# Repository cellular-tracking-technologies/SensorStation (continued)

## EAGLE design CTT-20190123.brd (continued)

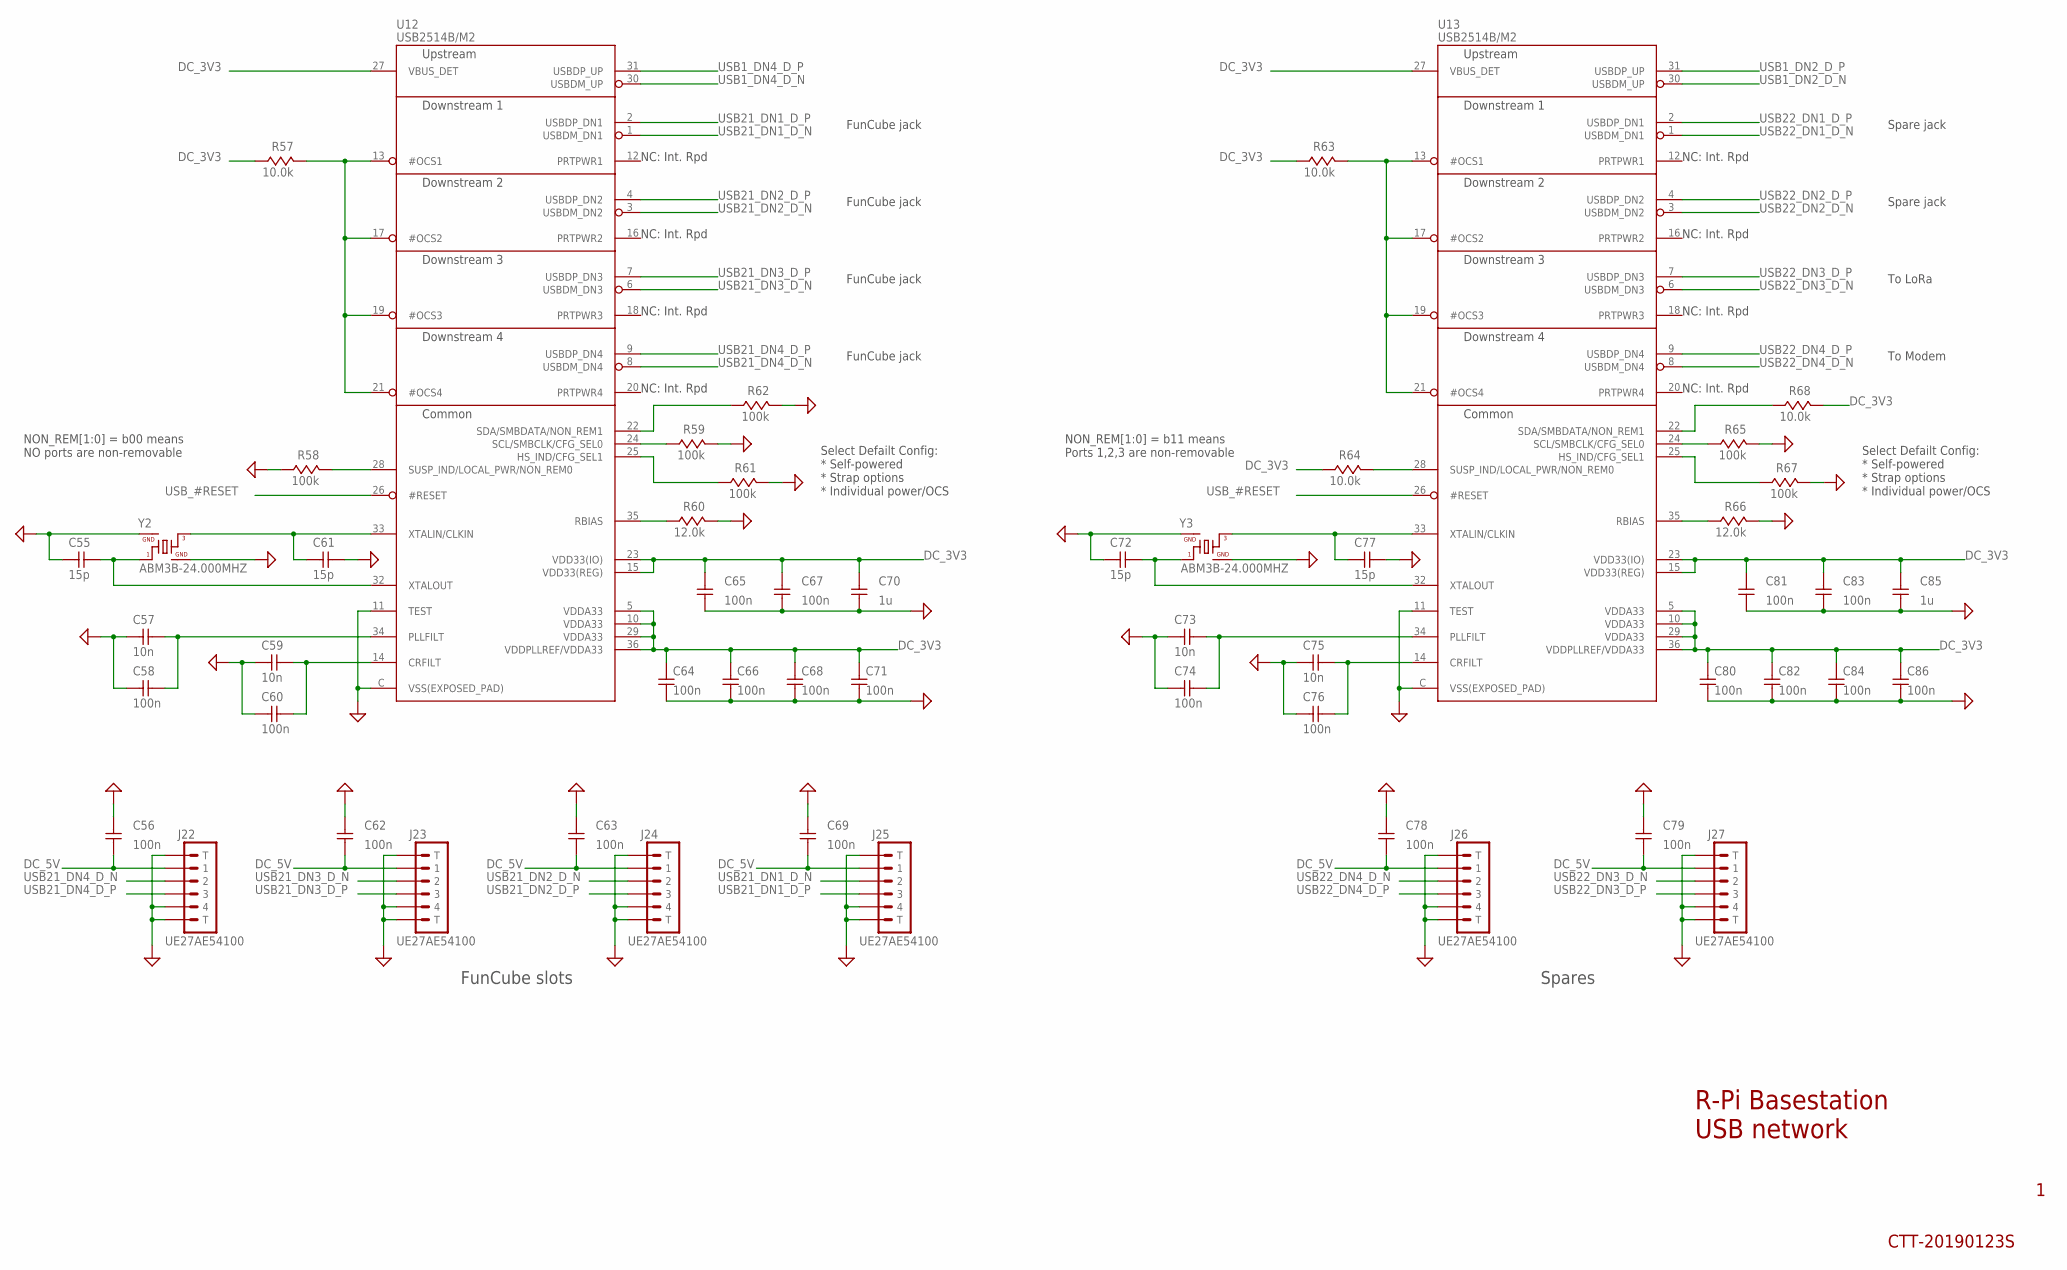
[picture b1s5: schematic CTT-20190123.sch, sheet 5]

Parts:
C55, C61, C72, C77: 15p; C0402_IPC7351_MED
C56, C58, C60, C62, C63, C64, C65, C66, C67, C68, C69, C71, C74, C76, C78, C79, C80, C81, C82, C83, C84, C86: 100n; C0402_IPC7351_MED
C57, C59, C73, C75: 10n; C0402_IPC7351_MED
C70, C85: 1u; C0603_IPC7351_MED
J22, J23, J24, J25, J26, J27: UE27AE54100
R57, R63, R64, R68: 10.0k; R0402_IPC7351_MED
R58, R59, R61, R62, R65, R67: 100k; R0402_IPC7351_MED
R60, R66: 12.0k; R0402_IPC7351_MED
U12, U13: USB2514B/M2; SQFN-36
Y2, Y3: ABM3B-24.000MHZ; ABM3B

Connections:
DC_3V3: C64.P$2 (2), C65.P$2 (2), C66.P$2 (2), C67.P$2 (2), C68.P$2 (2), C70.P$2 (2), C71.P$2 (2), C80.P$2 (2), C81.P$2 (2), C82.P$2 (2), C83.P$2 (2), C84.P$2 (2), C85.P$2 (2), C86.P$2 (2), R57.P$1 (1), R63.P$1 (1), R64.P$1 (1), R68.P$2 (2), U12.5 (VDDA33), U12.10 (VDDA33), U12.15 (VDD33(REG)), U12.23 (VDD33(IO)), U12.27 (VBUS_DET), U12.29 (VDDA33), U12.36 (VDDPLLREF/VDDA33), U13.5 (VDDA33), U13.10 (VDDA33), U13.15 (VDD33(REG)), U13.23 (VDD33(IO)), U13.27 (VBUS_DET), U13.29 (VDDA33), U13.36 (VDDPLLREF/VDDA33); also elsewhere on the board
DC_5V: C56.P$1 (1), C62.P$1 (1), C63.P$1 (1), C69.P$1 (1), C78.P$1 (1), C79.P$1 (1), J22.1, J23.1, J24.1, J25.1, J26.1, J27.1; also elsewhere on the board
GND: C55.P$1 (1), C56.P$2 (2), C57.P$1 (1), C58.P$1 (1), C59.P$1 (1), C60.P$1 (1), C61.P$2 (2), C62.P$2 (2), C63.P$2 (2), C64.P$1 (1), C65.P$1 (1), C66.P$1 (1), C67.P$1 (1), C68.P$1 (1), C69.P$2 (2), C70.P$1 (1), C71.P$1 (1), C72.P$1 (1), C73.P$1 (1), C74.P$1 (1), C75.P$1 (1), C76.P$1 (1), C77.P$2 (2), C78.P$2 (2), C79.P$2 (2), C80.P$1 (1), C81.P$1 (1), C82.P$1 (1), C83.P$1 (1), C84.P$1 (1), C85.P$1 (1), C86.P$1 (1), J22.4, J22.P$1 (T), J22.P$2 (T), J23.4, J23.P$1 (T), J23.P$2 (T), J24.4, J24.P$1 (T), J24.P$2 (T), J25.4, J25.P$1 (T), J25.P$2 (T), J26.4, J26.P$1 (T), J26.P$2 (T), J27.4, J27.P$1 (T), J27.P$2 (T), R58.P$1 (1), R59.P$2 (2), R60.P$2 (2), R61.P$2 (2), R62.P$2 (2), R65.P$2 (2), R66.P$2 (2), R67.P$2 (2), U12.11 (TEST), U12.C (VSS(EXPOSED_PAD)), U13.11 (TEST), U13.C (VSS(EXPOSED_PAD)), Y2.2, Y2.4, Y3.2, Y3.4; also elsewhere on the board
unnamed: C77.P$1 (1), U13.33 (XTALIN/CLKIN), Y3.3
unnamed: C72.P$2 (2), U13.32 (XTALOUT), Y3.1
unnamed: C61.P$1 (1), U12.33 (XTALIN/CLKIN), Y2.3
unnamed: C55.P$2 (2), U12.32 (XTALOUT), Y2.1
unnamed: C57.P$2 (2), C58.P$2 (2), U12.34 (PLLFILT)
unnamed: C73.P$2 (2), C74.P$2 (2), U13.34 (PLLFILT)
unnamed: C59.P$2 (2), C60.P$2 (2), U12.14 (CRFILT)
unnamed: R59.P$1 (1), U12.24 (SCL/SMBCLK/CFG_SEL0)
unnamed: C75.P$2 (2), C76.P$2 (2), U13.14 (CRFILT)
unnamed: R65.P$1 (1), U13.24 (SCL/SMBCLK/CFG_SEL0)
unnamed: R61.P$1 (1), U12.25 (HS_IND/CFG_SEL1)
unnamed: R67.P$1 (1), U13.25 (HS_IND/CFG_SEL1)
unnamed: R60.P$1 (1), U12.35 (RBIAS)
unnamed: R57.P$2 (2), U12.13 (#OCS1), U12.17 (#OCS2), U12.19 (#OCS3), U12.21 (#OCS4)
unnamed: R62.P$1 (1), U12.22 (SDA/SMBDATA/NON_REM1)
unnamed: R58.P$2 (2), U12.28 (SUSP_IND/LOCAL_PWR/NON_REM0)
unnamed: R66.P$1 (1), U13.35 (RBIAS)
unnamed: R63.P$2 (2), U13.13 (#OCS1), U13.17 (#OCS2), U13.19 (#OCS3), U13.21 (#OCS4)
unnamed: R68.P$1 (1), U13.22 (SDA/SMBDATA/NON_REM1)
unnamed: R64.P$2 (2), U13.28 (SUSP_IND/LOCAL_PWR/NON_REM0)
USB1_DN2_D_N: U13.30 (USBDM_UP); also elsewhere on the board
USB1_DN2_D_P: U13.31 (USBDP_UP); also elsewhere on the board
USB1_DN4_D_N: U12.30 (USBDM_UP); also elsewhere on the board
USB1_DN4_D_P: U12.31 (USBDP_UP); also elsewhere on the board
USB21_DN1_D_N: J25.2, U12.1 (USBDM_DN1)
USB21_DN1_D_P: J25.3, U12.2 (USBDP_DN1)
USB21_DN2_D_N: J24.2, U12.3 (USBDM_DN2)
USB21_DN2_D_P: J24.3, U12.4 (USBDP_DN2)
USB21_DN3_D_N: J23.2, U12.6 (USBDM_DN3)
USB21_DN3_D_P: J23.3, U12.7 (USBDP_DN3)
USB21_DN4_D_N: J22.2, U12.8 (USBDM_DN4)
USB21_DN4_D_P: J22.3, U12.9 (USBDP_DN4)
USB22_DN1_D_N: U13.1 (USBDM_DN1); also elsewhere on the board
USB22_DN1_D_P: U13.2 (USBDP_DN1); also elsewhere on the board
USB22_DN2_D_N: U13.3 (USBDM_DN2); also elsewhere on the board
USB22_DN2_D_P: U13.4 (USBDP_DN2); also elsewhere on the board
USB22_DN3_D_N: J27.2, U13.6 (USBDM_DN3)
USB22_DN3_D_P: J27.3, U13.7 (USBDP_DN3)
USB22_DN4_D_N: J26.2, U13.8 (USBDM_DN4)
USB22_DN4_D_P: J26.3, U13.9 (USBDP_DN4)
USB_#RESET: U12.26 (#RESET), U13.26 (#RESET); also elsewhere on the board

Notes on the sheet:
R-Pi Basestation USB network
CTT-20190123S
NC: Int. Rpd
Select Defailt Config: * Self-powered * Strap options * Individual power/OCS
NON_REM[1:0] = b00 means NO ports are non-removable
FunCube slots
NON_REM[1:0] = b11 means Ports 1,2,3 are non-removable
Spares
To Modem
To LoRa
Spare jack
FunCube jack

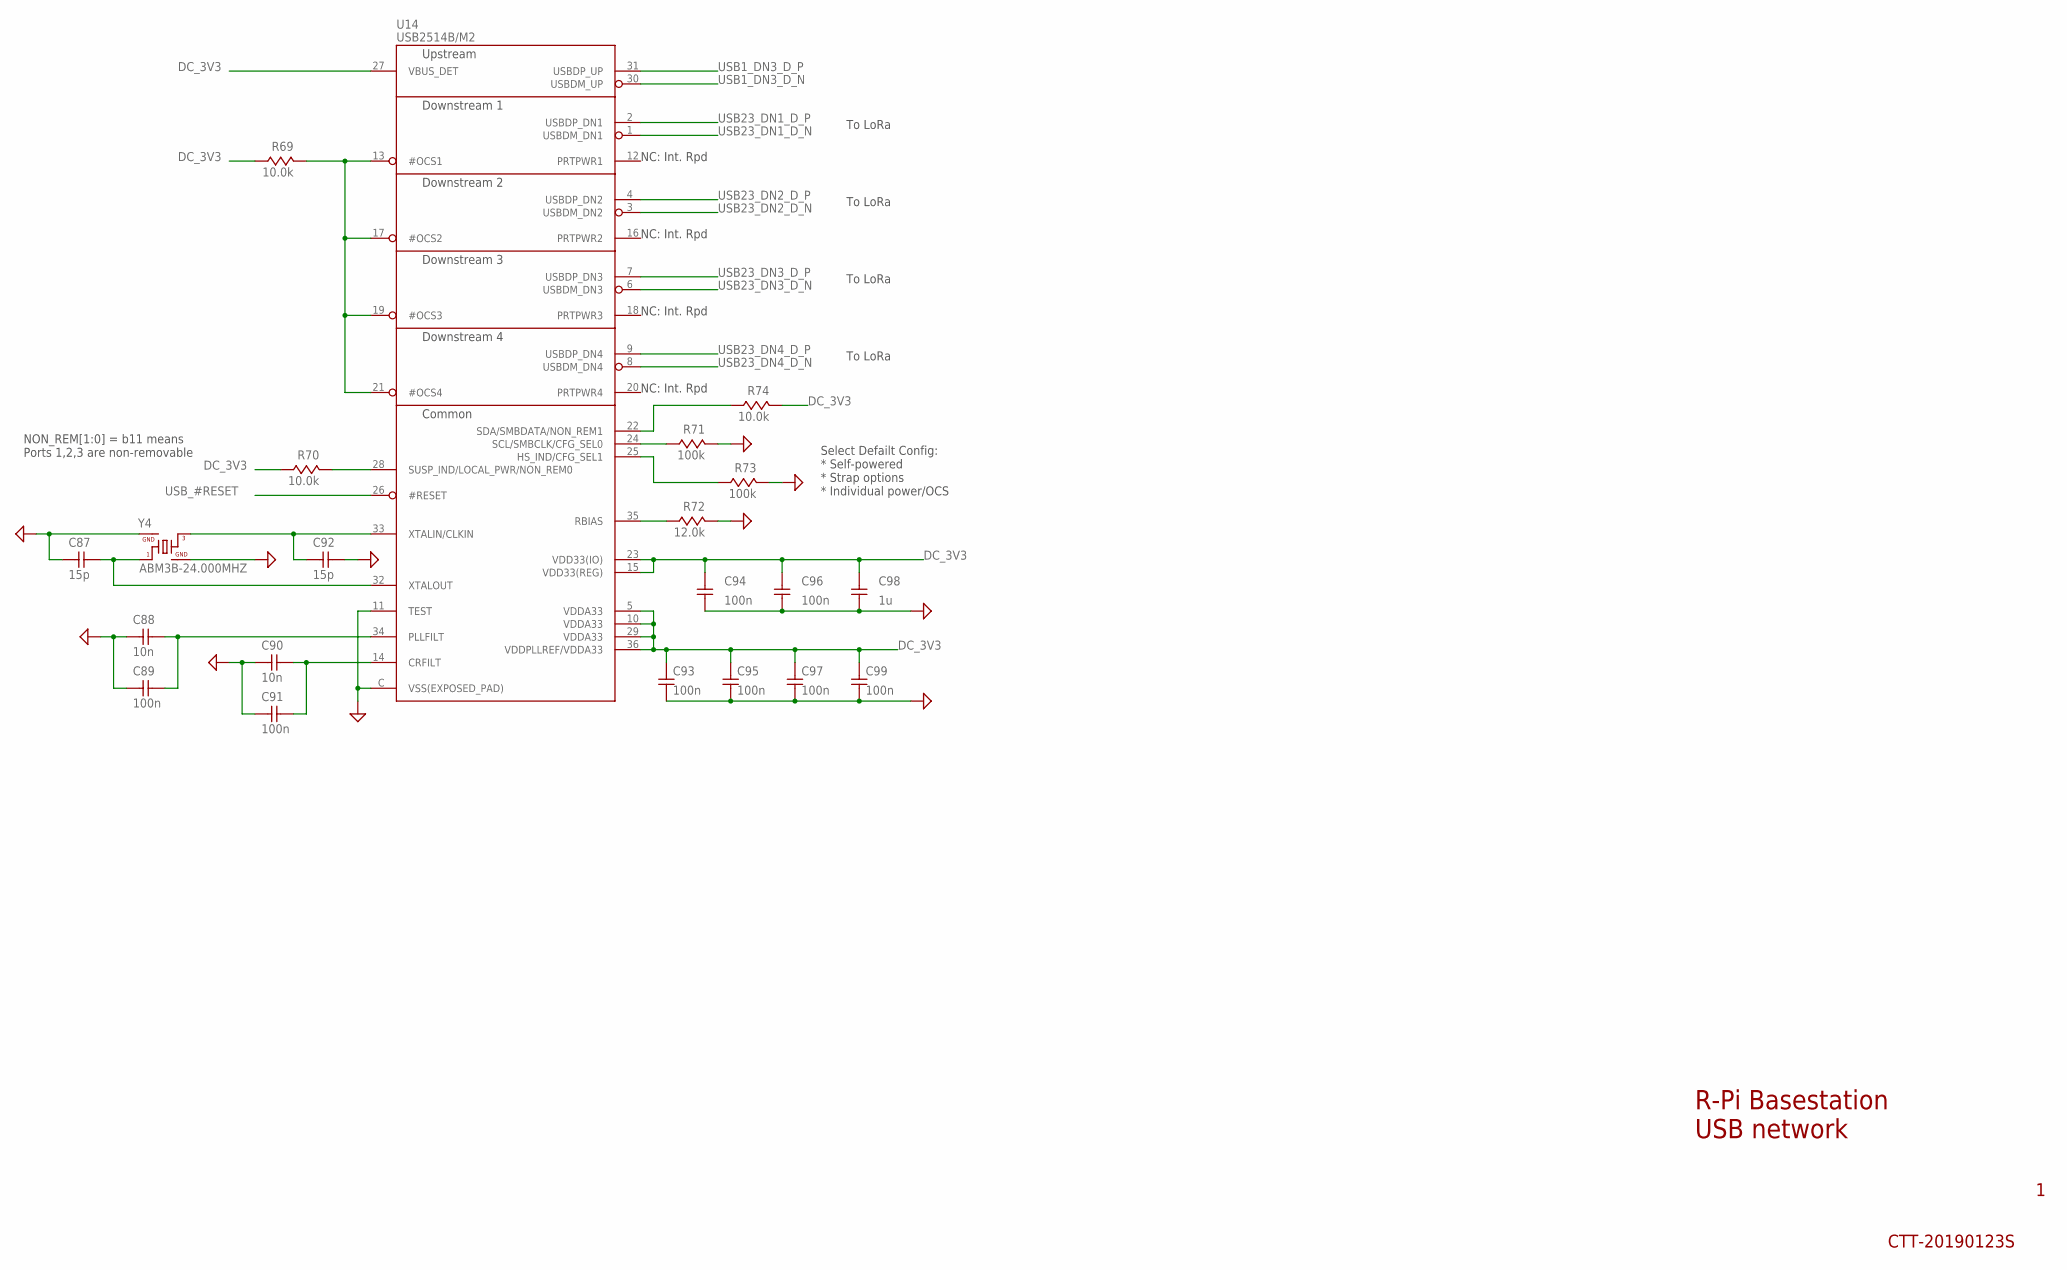
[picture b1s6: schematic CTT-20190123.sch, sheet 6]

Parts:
C87, C92: 15p; C0402_IPC7351_MED
C88, C90: 10n; C0402_IPC7351_MED
C89, C91, C93, C94, C95, C96, C97, C99: 100n; C0402_IPC7351_MED
C98: 1u; C0603_IPC7351_MED
R69, R70, R74: 10.0k; R0402_IPC7351_MED
R71, R73: 100k; R0402_IPC7351_MED
R72: 12.0k; R0402_IPC7351_MED
U14: USB2514B/M2; SQFN-36
Y4: ABM3B-24.000MHZ; ABM3B

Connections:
DC_3V3: C93.P$2 (2), C94.P$2 (2), C95.P$2 (2), C96.P$2 (2), C97.P$2 (2), C98.P$2 (2), C99.P$2 (2), R69.P$1 (1), R70.P$1 (1), R74.P$2 (2), U14.5 (VDDA33), U14.10 (VDDA33), U14.15 (VDD33(REG)), U14.23 (VDD33(IO)), U14.27 (VBUS_DET), U14.29 (VDDA33), U14.36 (VDDPLLREF/VDDA33); also elsewhere on the board
GND: C87.P$1 (1), C88.P$1 (1), C89.P$1 (1), C90.P$1 (1), C91.P$1 (1), C92.P$2 (2), C93.P$1 (1), C94.P$1 (1), C95.P$1 (1), C96.P$1 (1), C97.P$1 (1), C98.P$1 (1), C99.P$1 (1), R71.P$2 (2), R72.P$2 (2), R73.P$2 (2), U14.11 (TEST), U14.C (VSS(EXPOSED_PAD)), Y4.2, Y4.4; also elsewhere on the board
unnamed: C92.P$1 (1), U14.33 (XTALIN/CLKIN), Y4.3
unnamed: C87.P$2 (2), U14.32 (XTALOUT), Y4.1
unnamed: C88.P$2 (2), C89.P$2 (2), U14.34 (PLLFILT)
unnamed: C90.P$2 (2), C91.P$2 (2), U14.14 (CRFILT)
unnamed: R71.P$1 (1), U14.24 (SCL/SMBCLK/CFG_SEL0)
unnamed: R73.P$1 (1), U14.25 (HS_IND/CFG_SEL1)
unnamed: R72.P$1 (1), U14.35 (RBIAS)
unnamed: R69.P$2 (2), U14.13 (#OCS1), U14.17 (#OCS2), U14.19 (#OCS3), U14.21 (#OCS4)
unnamed: R74.P$1 (1), U14.22 (SDA/SMBDATA/NON_REM1)
unnamed: R70.P$2 (2), U14.28 (SUSP_IND/LOCAL_PWR/NON_REM0)
USB1_DN3_D_N: U14.30 (USBDM_UP); also elsewhere on the board
USB1_DN3_D_P: U14.31 (USBDP_UP); also elsewhere on the board
USB23_DN1_D_N: U14.1 (USBDM_DN1); also elsewhere on the board
USB23_DN1_D_P: U14.2 (USBDP_DN1); also elsewhere on the board
USB23_DN2_D_N: U14.3 (USBDM_DN2); also elsewhere on the board
USB23_DN2_D_P: U14.4 (USBDP_DN2); also elsewhere on the board
USB23_DN3_D_N: U14.6 (USBDM_DN3); also elsewhere on the board
USB23_DN3_D_P: U14.7 (USBDP_DN3); also elsewhere on the board
USB23_DN4_D_N: U14.8 (USBDM_DN4); also elsewhere on the board
USB23_DN4_D_P: U14.9 (USBDP_DN4); also elsewhere on the board
USB_#RESET: U14.26 (#RESET); also elsewhere on the board

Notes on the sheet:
R-Pi Basestation USB network
CTT-20190123S
NC: Int. Rpd
Select Defailt Config: * Self-powered * Strap options * Individual power/OCS
NON_REM[1:0] = b11 means Ports 1,2,3 are non-removable
To LoRa

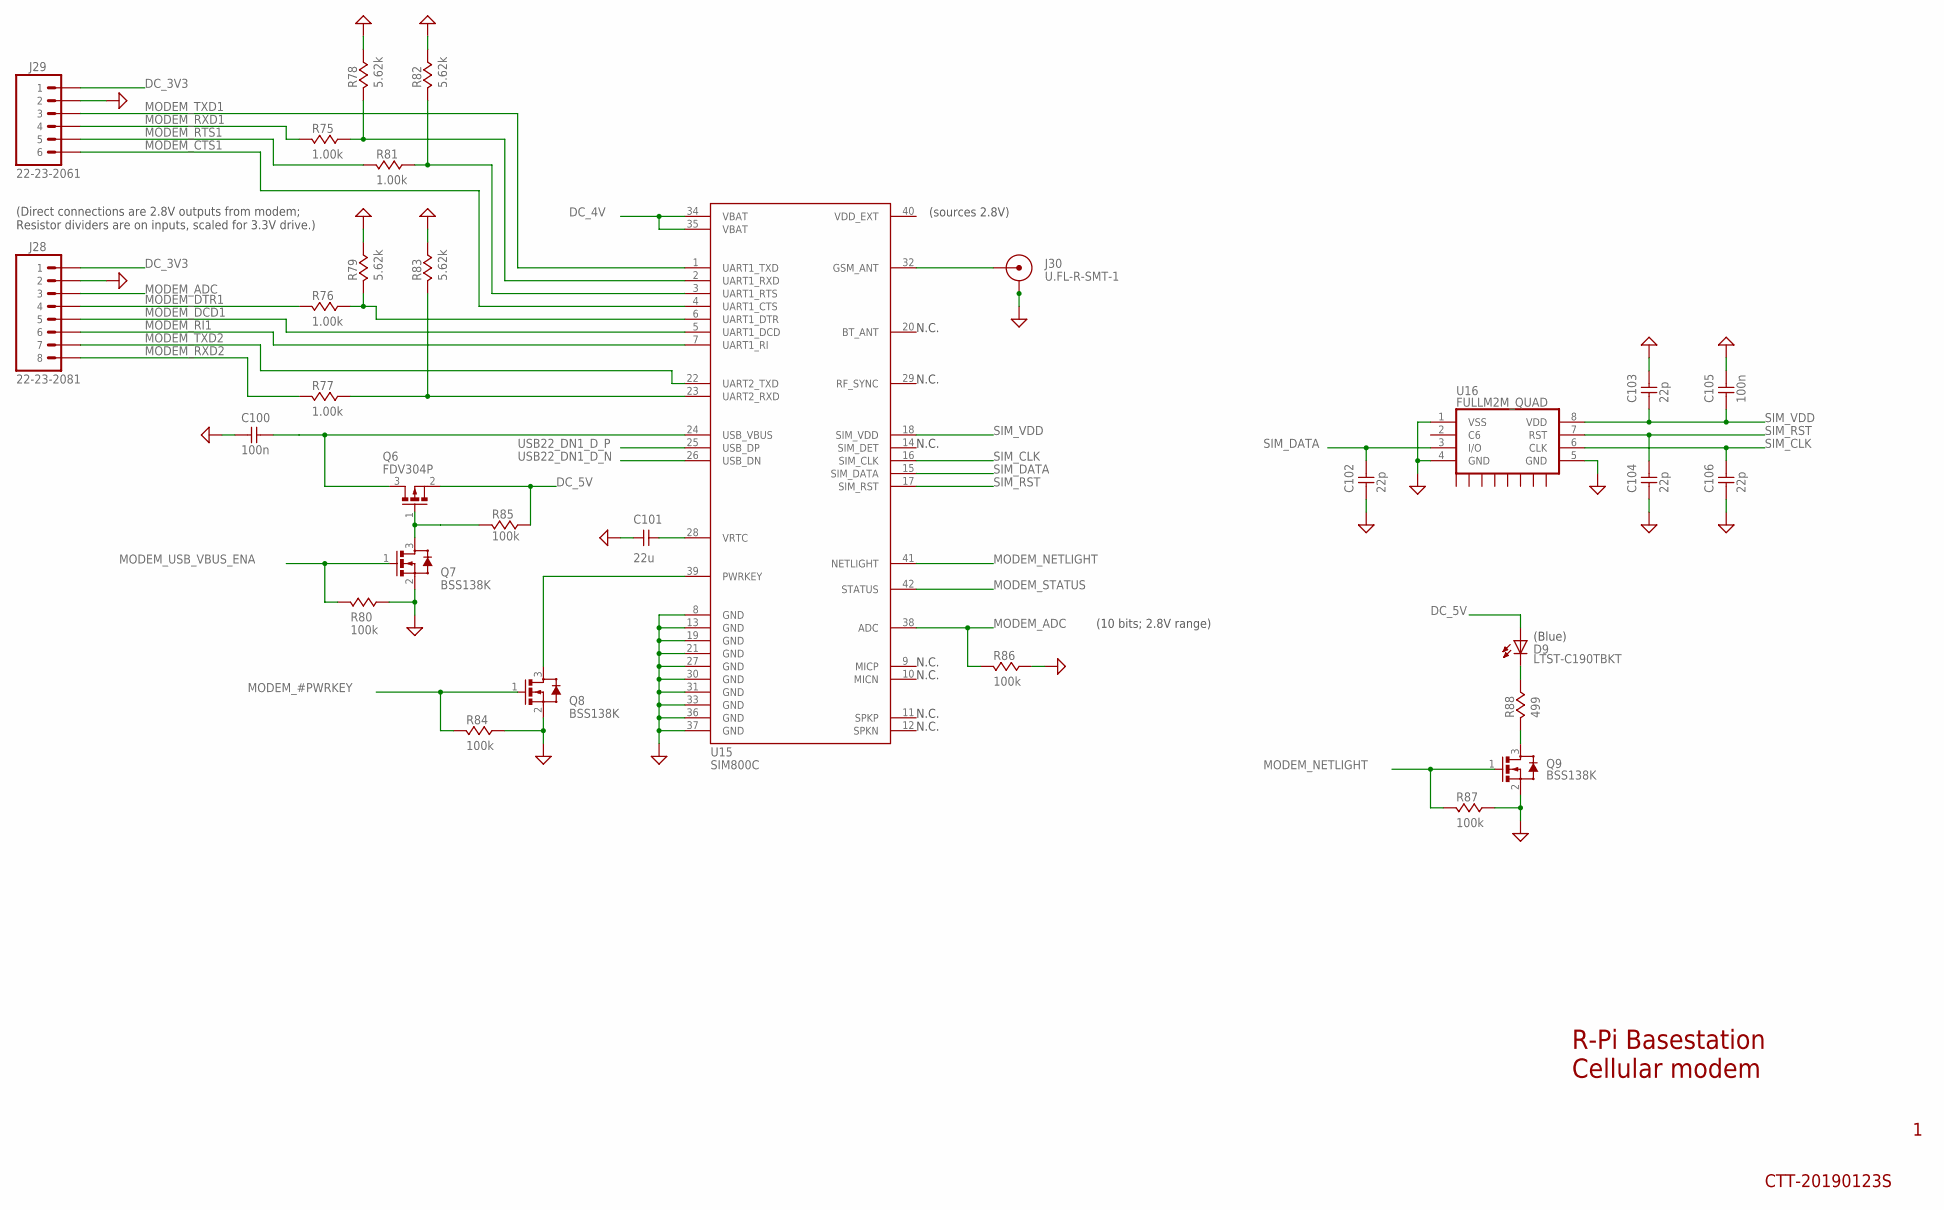
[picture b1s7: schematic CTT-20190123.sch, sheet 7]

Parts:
C100, C105: 100n; C0402_IPC7351_MED
C101: 22u; C0805
C102, C103, C104, C106: 22p; C0402_IPC7351_MED
D9: LTST-C190TBKT; LED0603
J28: 22-23-2081; MTA100-8
J29: 22-23-2061; MTA100-6
J30: U.FL-R-SMT-1
Q6: FDV304P; SOT-23
Q7, Q8, Q9: BSS138K; SOT-23
R75, R76, R77, R81: 1.00k; R0402_IPC7351_MED
R78, R79, R82, R83: 5.62k; R0402_IPC7351_MED
R80, R84, R85, R86, R87: 100k; R0402_IPC7351_MED
R88: 499; R0402_IPC7351_MED
U15: SIM800C
U16: FULLM2M_QUAD; MFF2

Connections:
DC_3V3: J28.1, J29.1; also elsewhere on the board
DC_4V: U15.34 (VBAT), U15.35 (VBAT); also elsewhere on the board
DC_5V: D9.A, Q6.2 (S), R85.P$1 (1); also elsewhere on the board
GND: C100.P$1 (1), C101.1, C102.P$1 (1), C103.P$2 (2), C104.P$1 (1), C105.P$2 (2), C106.P$1 (1), J28.2, J29.2, J30.GND, J30.GND@1 (GND), Q7.2 (S), Q8.2 (S), Q9.2 (S), R78.P$1 (1), R79.P$1 (1), R80.P$1 (1), R82.P$1 (1), R83.P$1 (1), R84.P$1 (1), R86.P$1 (1), R87.P$1 (1), U15.8 (GND), U15.13 (GND), U15.19 (GND), U15.21 (GND), U15.27 (GND), U15.30 (GND), U15.31 (GND), U15.33 (GND), U15.36 (GND), U15.37 (GND), U16.1 (VSS), U16.4 (GND), U16.5 (GND); also elsewhere on the board
MODEM_#PWRKEY: Q8.1 (G), R84.P$2 (2); also elsewhere on the board
MODEM_ADC: J28.3, R86.P$2 (2), U15.38 (ADC)
MODEM_CTS1: J29.6, U15.4 (UART1_CTS); also elsewhere on the board
MODEM_DCD1: J28.5, U15.5 (UART1_DCD)
MODEM_DTR1: J28.4, R76.P$2 (2)
MODEM_NETLIGHT: Q9.1 (G), R87.P$2 (2), U15.41 (NETLIGHT)
MODEM_RI1: J28.6, U15.7 (UART1_RI)
MODEM_RTS1: J29.5, R81.P$2 (2); also elsewhere on the board
MODEM_RXD1: J29.4, R75.P$2 (2); also elsewhere on the board
MODEM_RXD2: J28.8, R77.P$2 (2)
MODEM_STATUS: U15.42 (STATUS); also elsewhere on the board
MODEM_TXD1: J29.3, U15.1 (UART1_TXD); also elsewhere on the board
MODEM_TXD2: J28.7, U15.22 (UART2_TXD)
MODEM_USB_VBUS_ENA: Q7.1 (G), R80.P$2 (2); also elsewhere on the board
unnamed: Q8.3 (D), U15.39 (PWRKEY)
unnamed: C101.2, U15.28 (VRTC)
unnamed: C100.P$2 (2), Q6.3 (D), U15.24 (USB_VBUS)
unnamed: R77.P$1 (1), R83.P$2 (2), U15.23 (UART2_RXD)
unnamed: Q6.1 (G), Q7.3 (D), R85.P$2 (2)
unnamed: J30.SIG, U15.32 (GSM_ANT)
unnamed: R76.P$1 (1), R79.P$2 (2), U15.6 (UART1_DTR)
unnamed: D9.K, R88.P$1 (1)
unnamed: Q9.3 (D), R88.P$2 (2)
unnamed: R81.P$1 (1), R82.P$2 (2), U15.3 (UART1_RTS)
unnamed: R75.P$1 (1), R78.P$2 (2), U15.2 (UART1_RXD)
SIM_CLK: C106.P$2 (2), U15.16 (SIM_CLK), U16.6 (CLK)
SIM_DATA: C102.P$2 (2), U15.15 (SIM_DATA), U16.3 (I/O)
SIM_RST: C104.P$2 (2), U15.17 (SIM_RST), U16.7 (RST)
SIM_VDD: C103.P$1 (1), C105.P$1 (1), U15.18 (SIM_VDD), U16.8 (VDD)
USB22_DN1_D_N: U15.26 (USB_DN); also elsewhere on the board
USB22_DN1_D_P: U15.25 (USB_DP); also elsewhere on the board

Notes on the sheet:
N.C.
(sources 2.8V)
(Direct connections are 2.8V outputs from modem; Resistor dividers are on inputs, scaled for 3.3V drive.)
(10 bits; 2.8V range)
R-Pi Basestation Cellular modem
CTT-20190123S
(Blue)

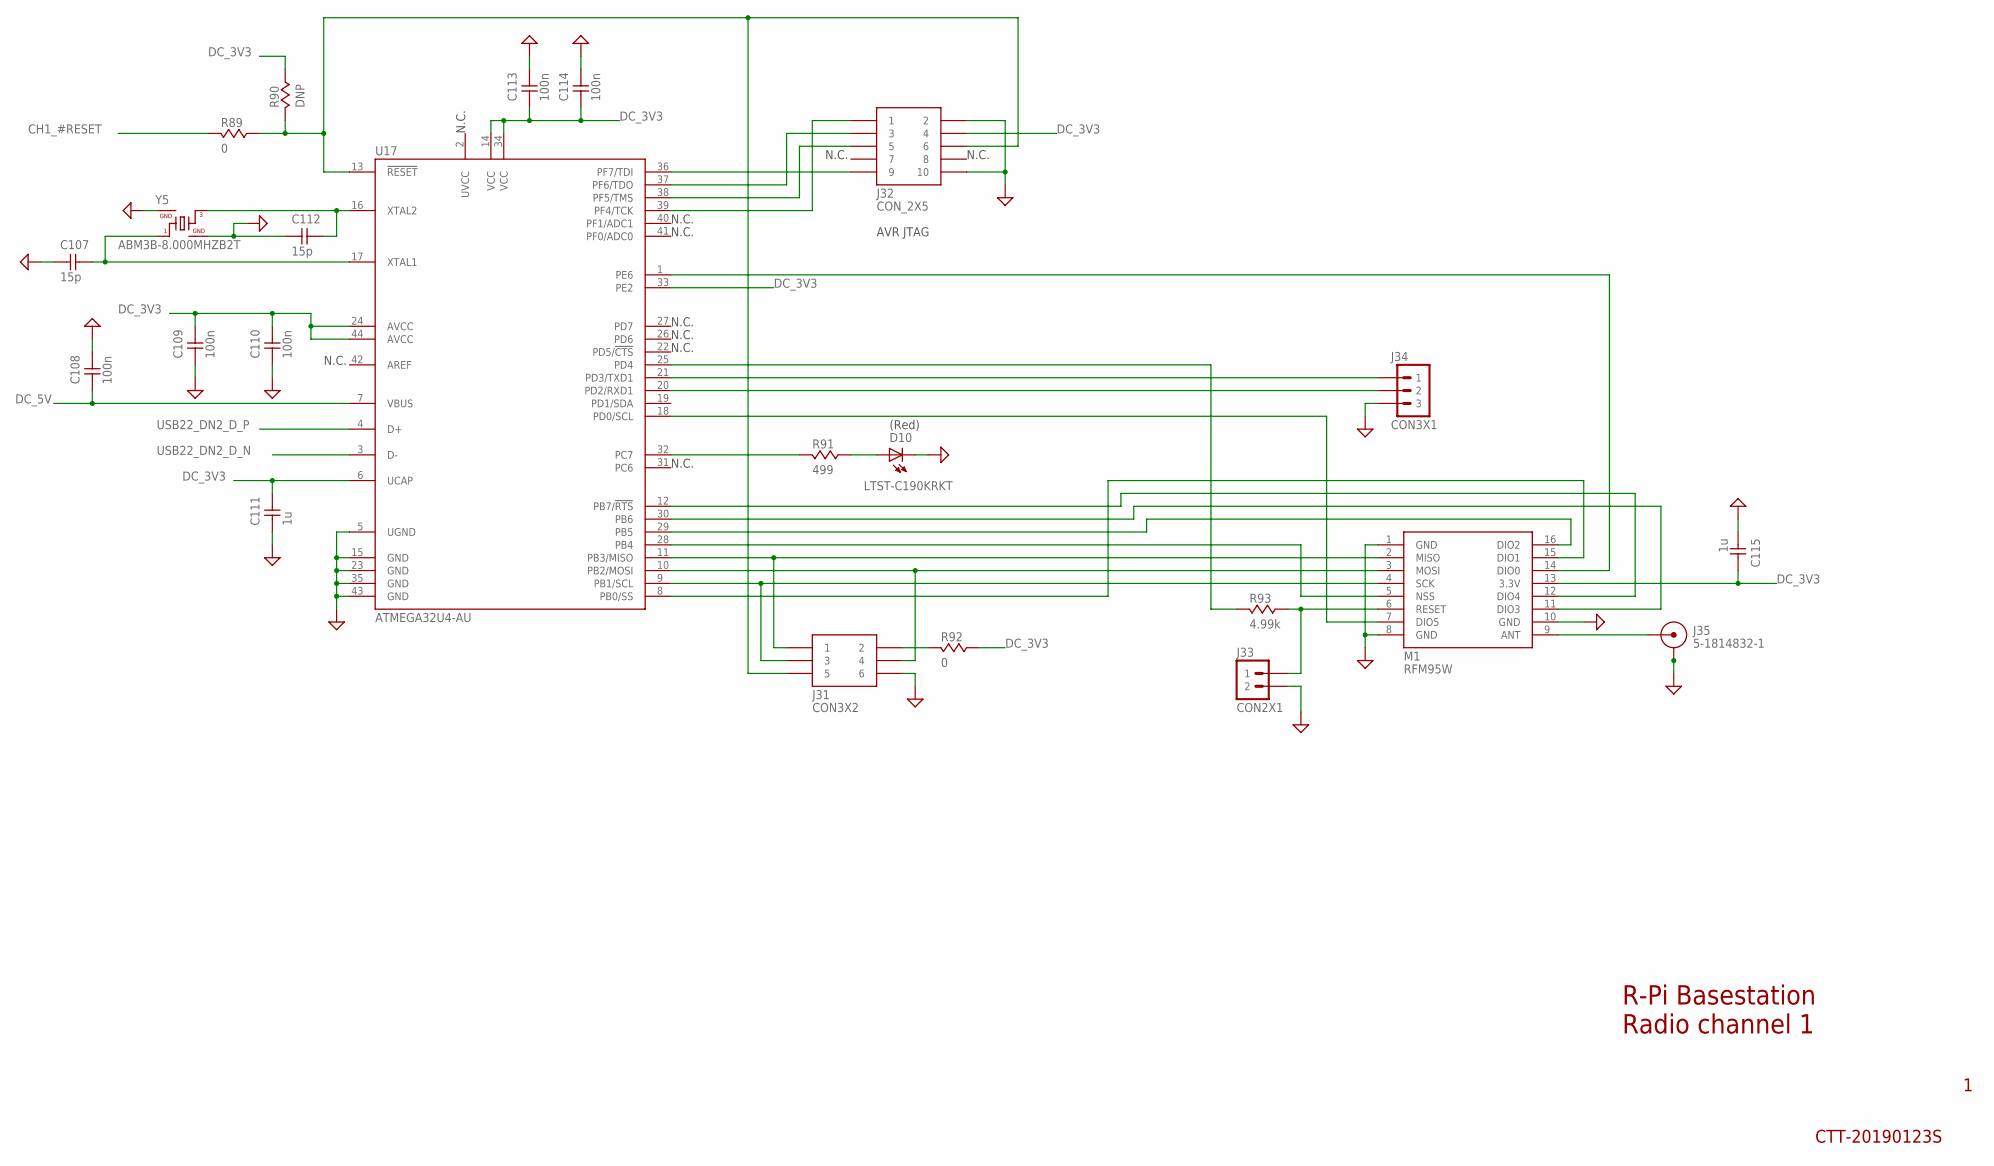
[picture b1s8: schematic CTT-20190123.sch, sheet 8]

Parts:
C107, C112: 15p; C0402_IPC7351_MED
C108, C109, C110, C113, C114: 100n; C0402_IPC7351_MED
C111, C115: 1u; C0603_IPC7351_MED
D10: LTST-C190KRKT; LED0603
J31: CON3X2
J32: CON_2X5; CON_5X2
J33: CON2X1
J34: CON3X1
J35: 5-1814832-1; CON_SMA_TH_VERT
M1: RFM95W
R89, R92: 0; R0402_IPC7351_MED
R90: DNP; R0402_IPC7351_MED
R91: 499; R0402_IPC7351_MED
R93: 4.99k; R0402_IPC7351_MED
U17: ATMEGA32U4-AU; TQFP44
Y5: ABM3B-8.000MHZB2T; ABM3B

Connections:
CH1_#RESET: R89.P$2 (2); also elsewhere on the board
DC_3V3: C109.P$2 (2), C110.P$2 (2), C111.P$2 (2), C113.P$1 (1), C114.P$1 (1), C115.P$2 (2), J32.4, M1.13 (3.3V), R90.P$1 (1), R92.P$1 (1), U17.6 (UCAP), U17.14 (VCC), U17.24 (AVCC), U17.33 (PE2), U17.34 (VCC), U17.44 (AVCC); also elsewhere on the board
DC_5V: C108.P$1 (1), U17.7 (VBUS); also elsewhere on the board
GND: C107.P$1 (1), C108.P$2 (2), C109.P$1 (1), C110.P$1 (1), C111.P$1 (1), C112.P$1 (1), C113.P$2 (2), C114.P$2 (2), C115.P$1 (1), D10.K, J31.6, J32.2, J32.10, J33.2, J34.3, J35.P$1 (GND), J35.P$2 (GND), J35.P$3 (GND), J35.P$4 (GND), M1.1 (GND), M1.8 (GND), M1.10 (GND), U17.5 (UGND), U17.15 (GND), U17.23 (GND), U17.35 (GND), U17.43 (GND), Y5.2, Y5.4; also elsewhere on the board
unnamed: C112.P$2 (2), U17.16 (XTAL2), Y5.3
unnamed: J32.1, U17.39 (PF4/TCK)
unnamed: C107.P$2 (2), U17.17 (XTAL1), Y5.1
unnamed: J31.5, J32.6, R89.P$1 (1), R90.P$2 (2), U17.13 (!RESET)
unnamed: J32.5, U17.38 (PF5/TMS)
unnamed: J32.3, U17.37 (PF6/TDO)
unnamed: J32.9, U17.36 (PF7/TDI)
unnamed: J31.1, M1.2 (MISO), U17.11 (PB3/MISO)
unnamed: J35.C (SIG), M1.9 (ANT)
unnamed: J31.4, M1.3 (MOSI), U17.10 (PB2/MOSI)
unnamed: J31.3, M1.4 (SCK), U17.9 (PB1/SCL)
unnamed: J33.1, M1.6 (RESET), R93.P$1 (1)
unnamed: R93.P$2 (2), U17.25 (PD4)
unnamed: J34.1, U17.21 (PD3/TXD1)
unnamed: J34.2, U17.20 (PD2/RXD1)
unnamed: J31.2, R92.P$2 (2)
unnamed: M1.5 (NSS), U17.28 (PB4)
unnamed: M1.16 (DIO2), U17.29 (PB5)
unnamed: M1.11 (DIO3), U17.30 (PB6)
unnamed: M1.12 (DIO4), U17.12 (PB7/!RTS)
unnamed: M1.7 (DIO5), U17.18 (PD0/SCL)
unnamed: M1.14 (DIO0), U17.1 (PE6)
unnamed: M1.15 (DIO1), U17.8 (PB0/SS)
unnamed: R91.P$2 (2), U17.32 (PC7)
unnamed: D10.A, R91.P$1 (1)
USB22_DN2_D_N: U17.3 (D-); also elsewhere on the board
USB22_DN2_D_P: U17.4 (D+); also elsewhere on the board

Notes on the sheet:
N.C.
R-Pi Basestation Radio channel 1
CTT-20190123S
(Red)
AVR JTAG

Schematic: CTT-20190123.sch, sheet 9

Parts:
C116, C121: 15p; C0402_IPC7351_MED
C117, C118, C119, C122, C123: 100n; C0402_IPC7351_MED
C120, C124: 1u; C0603_IPC7351_MED
D11: LTST-C190KRKT; LED0603
J36: CON3X2
J37: CON_2X5; CON_5X2
J38: CON2X1
J39: CON3X1
J40: 5-1814832-1; CON_SMA_TH_VERT
M2: RFM95W
R94, R97: 0; R0402_IPC7351_MED
R95: DNP; R0402_IPC7351_MED
R96: 499; R0402_IPC7351_MED
R98: 4.99k; R0402_IPC7351_MED
U18: ATMEGA32U4-AU; TQFP44
Y6: ABM3B-8.000MHZB2T; ABM3B

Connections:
CH2_#RESET: R94.P$2 (2); also elsewhere on the board
DC_3V3: C118.P$2 (2), C119.P$2 (2), C120.P$2 (2), C122.P$1 (1), C123.P$1 (1), C124.P$2 (2), J37.4, M2.13 (3.3V), R95.P$1 (1), R97.P$1 (1), U18.6 (UCAP), U18.14 (VCC), U18.24 (AVCC), U18.33 (PE2), U18.34 (VCC), U18.44 (AVCC); also elsewhere on the board
DC_5V: C117.P$1 (1), U18.7 (VBUS); also elsewhere on the board
GND: C116.P$1 (1), C117.P$2 (2), C118.P$1 (1), C119.P$1 (1), C120.P$1 (1), C121.P$1 (1), C122.P$2 (2), C123.P$2 (2), C124.P$1 (1), D11.K, J36.6, J37.2, J37.10, J38.2, J39.3, J40.P$1 (GND), J40.P$2 (GND), J40.P$3 (GND), J40.P$4 (GND), M2.1 (GND), M2.8 (GND), M2.10 (GND), U18.5 (UGND), U18.15 (GND), U18.23 (GND), U18.35 (GND), U18.43 (GND), Y6.2, Y6.4; also elsewhere on the board
unnamed: C121.P$2 (2), U18.16 (XTAL2), Y6.3
unnamed: C116.P$2 (2), U18.17 (XTAL1), Y6.1
unnamed: J36.5, J37.6, R94.P$1 (1), R95.P$2 (2), U18.13 (!RESET)
unnamed: J37.1, U18.39 (PF4/TCK)
unnamed: J37.5, U18.38 (PF5/TMS)
unnamed: J37.3, U18.37 (PF6/TDO)
unnamed: J37.9, U18.36 (PF7/TDI)
unnamed: J40.C (SIG), M2.9 (ANT)
unnamed: J36.1, M2.2 (MISO), U18.11 (PB3/MISO)
unnamed: J36.4, M2.3 (MOSI), U18.10 (PB2/MOSI)
unnamed: J36.3, M2.4 (SCK), U18.9 (PB1/SCL)
unnamed: J38.1, M2.6 (RESET), R98.P$1 (1)
unnamed: R98.P$2 (2), U18.25 (PD4)
unnamed: J39.1, U18.21 (PD3/TXD1)
unnamed: J39.2, U18.20 (PD2/RXD1)
unnamed: J36.2, R97.P$2 (2)
unnamed: M2.5 (NSS), U18.28 (PB4)
unnamed: M2.16 (DIO2), U18.29 (PB5)
unnamed: M2.11 (DIO3), U18.30 (PB6)
unnamed: M2.12 (DIO4), U18.12 (PB7/!RTS)
unnamed: M2.7 (DIO5), U18.18 (PD0/SCL)
unnamed: M2.14 (DIO0), U18.1 (PE6)
unnamed: M2.15 (DIO1), U18.8 (PB0/SS)
unnamed: R96.P$2 (2), U18.32 (PC7)
unnamed: D11.A, R96.P$1 (1)
USB23_DN1_D_N: U18.3 (D-); also elsewhere on the board
USB23_DN1_D_P: U18.4 (D+); also elsewhere on the board

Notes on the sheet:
N.C.
R-Pi Basestation Radio channel 2
CTT-20190123S
(Red)
AVR JTAG

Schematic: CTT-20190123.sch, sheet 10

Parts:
C125, C130: 15p; C0402_IPC7351_MED
C126, C127, C128, C131, C132: 100n; C0402_IPC7351_MED
C129, C133: 1u; C0603_IPC7351_MED
D12: LTST-C190KRKT; LED0603
J41: CON3X2
J42: CON_2X5; CON_5X2
J43: CON2X1
J44: CON3X1
J45: 5-1814832-1; CON_SMA_TH_VERT
M3: RFM95W
R99, R102: 0; R0402_IPC7351_MED
R100: DNP; R0402_IPC7351_MED
R101: 499; R0402_IPC7351_MED
R103: 4.99k; R0402_IPC7351_MED
U19: ATMEGA32U4-AU; TQFP44
Y7: ABM3B-8.000MHZB2T; ABM3B

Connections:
CH3_#RESET: R99.P$2 (2); also elsewhere on the board
DC_3V3: C127.P$2 (2), C128.P$2 (2), C129.P$2 (2), C131.P$1 (1), C132.P$1 (1), C133.P$2 (2), J42.4, M3.13 (3.3V), R100.P$1 (1), R102.P$1 (1), U19.6 (UCAP), U19.14 (VCC), U19.24 (AVCC), U19.33 (PE2), U19.34 (VCC), U19.44 (AVCC); also elsewhere on the board
DC_5V: C126.P$1 (1), U19.7 (VBUS); also elsewhere on the board
GND: C125.P$1 (1), C126.P$2 (2), C127.P$1 (1), C128.P$1 (1), C129.P$1 (1), C130.P$1 (1), C131.P$2 (2), C132.P$2 (2), C133.P$1 (1), D12.K, J41.6, J42.2, J42.10, J43.2, J44.3, J45.P$1 (GND), J45.P$2 (GND), J45.P$3 (GND), J45.P$4 (GND), M3.1 (GND), M3.8 (GND), M3.10 (GND), U19.5 (UGND), U19.15 (GND), U19.23 (GND), U19.35 (GND), U19.43 (GND), Y7.2, Y7.4; also elsewhere on the board
unnamed: C130.P$2 (2), U19.16 (XTAL2), Y7.3
unnamed: C125.P$2 (2), U19.17 (XTAL1), Y7.1
unnamed: J41.5, J42.6, R99.P$1 (1), R100.P$2 (2), U19.13 (!RESET)
unnamed: J42.1, U19.39 (PF4/TCK)
unnamed: J42.5, U19.38 (PF5/TMS)
unnamed: J42.3, U19.37 (PF6/TDO)
unnamed: J42.9, U19.36 (PF7/TDI)
unnamed: J45.C (SIG), M3.9 (ANT)
unnamed: J41.1, M3.2 (MISO), U19.11 (PB3/MISO)
unnamed: J41.4, M3.3 (MOSI), U19.10 (PB2/MOSI)
unnamed: J41.3, M3.4 (SCK), U19.9 (PB1/SCL)
unnamed: J43.1, M3.6 (RESET), R103.P$1 (1)
unnamed: R103.P$2 (2), U19.25 (PD4)
unnamed: J44.1, U19.21 (PD3/TXD1)
unnamed: J44.2, U19.20 (PD2/RXD1)
unnamed: J41.2, R102.P$2 (2)
unnamed: M3.5 (NSS), U19.28 (PB4)
unnamed: M3.16 (DIO2), U19.29 (PB5)
unnamed: M3.11 (DIO3), U19.30 (PB6)
unnamed: M3.12 (DIO4), U19.12 (PB7/!RTS)
unnamed: M3.7 (DIO5), U19.18 (PD0/SCL)
unnamed: M3.14 (DIO0), U19.1 (PE6)
unnamed: M3.15 (DIO1), U19.8 (PB0/SS)
unnamed: R101.P$2 (2), U19.32 (PC7)
unnamed: D12.A, R101.P$1 (1)
USB23_DN2_D_N: U19.3 (D-); also elsewhere on the board
USB23_DN2_D_P: U19.4 (D+); also elsewhere on the board

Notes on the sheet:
N.C.
R-Pi Basestation Radio channel 3
CTT-20190123S
(Red)
AVR JTAG

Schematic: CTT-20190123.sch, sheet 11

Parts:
C134, C139: 15p; C0402_IPC7351_MED
C135, C136, C137, C140, C141: 100n; C0402_IPC7351_MED
C138, C142: 1u; C0603_IPC7351_MED
D13: LTST-C190KRKT; LED0603
J46: CON3X2
J47: CON_2X5; CON_5X2
J48: CON2X1
J49: CON3X1
J50: 5-1814832-1; CON_SMA_TH_VERT
M4: RFM95W
R104, R107: 0; R0402_IPC7351_MED
R105: DNP; R0402_IPC7351_MED
R106: 499; R0402_IPC7351_MED
R108: 4.99k; R0402_IPC7351_MED
U20: ATMEGA32U4-AU; TQFP44
Y8: ABM3B-8.000MHZB2T; ABM3B

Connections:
CH4_#RESET: R104.P$2 (2); also elsewhere on the board
DC_3V3: C136.P$2 (2), C137.P$2 (2), C138.P$2 (2), C140.P$1 (1), C141.P$1 (1), C142.P$2 (2), J47.4, M4.13 (3.3V), R105.P$1 (1), R107.P$1 (1), U20.6 (UCAP), U20.14 (VCC), U20.24 (AVCC), U20.33 (PE2), U20.34 (VCC), U20.44 (AVCC); also elsewhere on the board
DC_5V: C135.P$1 (1), U20.7 (VBUS); also elsewhere on the board
GND: C134.P$1 (1), C135.P$2 (2), C136.P$1 (1), C137.P$1 (1), C138.P$1 (1), C139.P$1 (1), C140.P$2 (2), C141.P$2 (2), C142.P$1 (1), D13.K, J46.6, J47.2, J47.10, J48.2, J49.3, J50.P$1 (GND), J50.P$2 (GND), J50.P$3 (GND), J50.P$4 (GND), M4.1 (GND), M4.8 (GND), M4.10 (GND), U20.5 (UGND), U20.15 (GND), U20.23 (GND), U20.35 (GND), U20.43 (GND), Y8.2, Y8.4; also elsewhere on the board
unnamed: C139.P$2 (2), U20.16 (XTAL2), Y8.3
unnamed: C134.P$2 (2), U20.17 (XTAL1), Y8.1
unnamed: J46.5, J47.6, R104.P$1 (1), R105.P$2 (2), U20.13 (!RESET)
unnamed: J47.1, U20.39 (PF4/TCK)
unnamed: J47.5, U20.38 (PF5/TMS)
unnamed: J47.3, U20.37 (PF6/TDO)
unnamed: J47.9, U20.36 (PF7/TDI)
unnamed: J50.C (SIG), M4.9 (ANT)
unnamed: J46.1, M4.2 (MISO), U20.11 (PB3/MISO)
unnamed: J46.4, M4.3 (MOSI), U20.10 (PB2/MOSI)
unnamed: J46.3, M4.4 (SCK), U20.9 (PB1/SCL)
unnamed: J48.1, M4.6 (RESET), R108.P$1 (1)
unnamed: R108.P$2 (2), U20.25 (PD4)
unnamed: J49.1, U20.21 (PD3/TXD1)
unnamed: J49.2, U20.20 (PD2/RXD1)
unnamed: J46.2, R107.P$2 (2)
unnamed: M4.5 (NSS), U20.28 (PB4)
unnamed: M4.16 (DIO2), U20.29 (PB5)
unnamed: M4.11 (DIO3), U20.30 (PB6)
unnamed: M4.12 (DIO4), U20.12 (PB7/!RTS)
unnamed: M4.7 (DIO5), U20.18 (PD0/SCL)
unnamed: M4.14 (DIO0), U20.1 (PE6)
unnamed: M4.15 (DIO1), U20.8 (PB0/SS)
unnamed: R106.P$2 (2), U20.32 (PC7)
unnamed: D13.A, R106.P$1 (1)
USB23_DN3_D_N: U20.3 (D-); also elsewhere on the board
USB23_DN3_D_P: U20.4 (D+); also elsewhere on the board

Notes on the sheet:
N.C.
R-Pi Basestation Radio channel 4
CTT-20190123S
(Red)
AVR JTAG

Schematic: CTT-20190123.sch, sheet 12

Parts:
C143, C148: 15p; C0402_IPC7351_MED
C144, C145, C146, C149, C150: 100n; C0402_IPC7351_MED
C147, C151: 1u; C0603_IPC7351_MED
D14: LTST-C190KRKT; LED0603
J51: CON3X2
J52: CON_2X5; CON_5X2
J53: CON2X1
J54: CON3X1
J55: 5-1814832-1; CON_SMA_TH_VERT
M5: RFM95W
R109, R112: 0; R0402_IPC7351_MED
R110: DNP; R0402_IPC7351_MED
R111: 499; R0402_IPC7351_MED
R113: 4.99k; R0402_IPC7351_MED
U21: ATMEGA32U4-AU; TQFP44
Y9: ABM3B-8.000MHZB2T; ABM3B

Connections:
CH5_#RESET: R109.P$2 (2); also elsewhere on the board
DC_3V3: C145.P$2 (2), C146.P$2 (2), C147.P$2 (2), C149.P$1 (1), C150.P$1 (1), C151.P$2 (2), J52.4, M5.13 (3.3V), R110.P$1 (1), R112.P$1 (1), U21.6 (UCAP), U21.14 (VCC), U21.24 (AVCC), U21.33 (PE2), U21.34 (VCC), U21.44 (AVCC); also elsewhere on the board
DC_5V: C144.P$1 (1), U21.7 (VBUS); also elsewhere on the board
GND: C143.P$1 (1), C144.P$2 (2), C145.P$1 (1), C146.P$1 (1), C147.P$1 (1), C148.P$1 (1), C149.P$2 (2), C150.P$2 (2), C151.P$1 (1), D14.K, J51.6, J52.2, J52.10, J53.2, J54.3, J55.P$1 (GND), J55.P$2 (GND), J55.P$3 (GND), J55.P$4 (GND), M5.1 (GND), M5.8 (GND), M5.10 (GND), U21.5 (UGND), U21.15 (GND), U21.23 (GND), U21.35 (GND), U21.43 (GND), Y9.2, Y9.4; also elsewhere on the board
unnamed: C148.P$2 (2), U21.16 (XTAL2), Y9.3
unnamed: C143.P$2 (2), U21.17 (XTAL1), Y9.1
unnamed: J51.5, J52.6, R109.P$1 (1), R110.P$2 (2), U21.13 (!RESET)
unnamed: J52.1, U21.39 (PF4/TCK)
unnamed: J52.5, U21.38 (PF5/TMS)
unnamed: J52.3, U21.37 (PF6/TDO)
unnamed: J52.9, U21.36 (PF7/TDI)
unnamed: J55.C (SIG), M5.9 (ANT)
unnamed: J51.1, M5.2 (MISO), U21.11 (PB3/MISO)
unnamed: J51.4, M5.3 (MOSI), U21.10 (PB2/MOSI)
unnamed: J51.3, M5.4 (SCK), U21.9 (PB1/SCL)
unnamed: J53.1, M5.6 (RESET), R113.P$1 (1)
unnamed: R113.P$2 (2), U21.25 (PD4)
unnamed: J54.1, U21.21 (PD3/TXD1)
unnamed: J54.2, U21.20 (PD2/RXD1)
unnamed: J51.2, R112.P$2 (2)
unnamed: M5.5 (NSS), U21.28 (PB4)
unnamed: M5.16 (DIO2), U21.29 (PB5)
unnamed: M5.11 (DIO3), U21.30 (PB6)
unnamed: M5.12 (DIO4), U21.12 (PB7/!RTS)
unnamed: M5.7 (DIO5), U21.18 (PD0/SCL)
unnamed: M5.14 (DIO0), U21.1 (PE6)
unnamed: M5.15 (DIO1), U21.8 (PB0/SS)
unnamed: R111.P$2 (2), U21.32 (PC7)
unnamed: D14.A, R111.P$1 (1)
USB23_DN4_D_N: U21.3 (D-); also elsewhere on the board
USB23_DN4_D_P: U21.4 (D+); also elsewhere on the board

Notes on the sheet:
N.C.
R-Pi Basestation Radio channel 5
CTT-20190123S
(Red)
AVR JTAG
